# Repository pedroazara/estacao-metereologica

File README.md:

# Skylog — Estação Meteorológica Móvel

O Skylog é uma estação portátil para coletar dados ambientais durante
percursos. O sistema combina sensores conectados a um ESP32 com os recursos do
telefone, registra cada coleta localmente e envia os resultados para uma base
com site de visualização e análise.

## Versão documentada

Estado local analisado em **10/10/2026**, baseado no commit
`2cd59777b90f2dd33dc27cc1e1f5b2505c5105bb`, com alterações locais anteriores.
A V1 é uma meta de montagem; o aplicativo declara `1.0.0+1`.
Consulte a [documentação técnica consolidada](docs/versoes/2026-10-10-2cd5977-local/documentacao-tecnica.md) e o
[inventário de READMEs](docs/versoes/2026-10-10-2cd5977-local/cobertura-readmes.md).

## Estado da versão 1

O **aplicativo**, o **site** e o **sistema de coleta e sincronização** têm
implementação e testes locais. A V1 ainda precisa de integração de software e
validação física, além de finalizar o hardware:

- integrar ENS160+AHT21 no firmware principal, contrato BLE, aplicativo e base;
- alinhar o firmware ao conversor automático e à retirada dos sensores antigos;
- concluir o projeto da placa de circuito impresso;
- usinar a placa na CNC e montar os componentes;
- validar o conjunto completo de sensores;
- projetar e imprimir a caixa.

O firmware atual ainda consulta WTGAHRS3, KY-013 e KY-038, e o aplicativo
oferece KY-013/KY-038 na seleção. O ENS160+AHT21 existe apenas em sketch de
teste; ainda não é transmitido pelo firmware principal nem selecionável no app.
O som do telefone fica no JSONL, mas ainda não alimenta a medida de ruído no mapa.

## Sensores definidos para a montagem V1

| Origem | Sensor ou recurso | Medições |
|---|---|---|
| Estação | Sensor ambiental RS485 | Temperatura e umidade |
| Estação | KY-028 | Temperatura auxiliar |
| Estação | ENS160 + AHT21 | eCO₂ estimado, TVOC, índice de qualidade do ar, temperatura e umidade de compensação |
| Estação | GY-302 / BH1750 | Luminosidade em lux |
| Telefone | GPS | Posição, percurso, velocidade e rumo |
| Telefone | Microfone | Nível sonoro, sem armazenar o áudio |

O ENS160 é um sensor de qualidade do ar. O valor de eCO₂ é uma estimativa
calculada a partir dos gases detectados, não uma medição direta da concentração
de dióxido de carbono. O AHT21 fornece temperatura e umidade para compensar as
leituras do ENS160.

## Funcionamento

```text
Sensor RS485 ────────────┐
KY-028 ──────────────────┤
ENS160 + AHT21 (previsto)┼── ESP32 ── Bluetooth ── aplicativo
GY-302 / BH1750 ─────────┘                           + GPS do telefone
                                                     + nível sonoro
                                                            │
                                                    coleta em JSONL
                                                            │
                                                sincronização pela rede
                                                            │
                                                            ▼
                                               base de processamento
                                                            │
                                                            ▼
                                                  site de visualização
```

O ESP32 lê RS485, KY-028 e BH1750 e transmite os dados ao aplicativo por
Bluetooth Low Energy. O aplicativo acrescenta a localização e o nível sonoro
obtidos pelo telefone, registra a coleta e mantém o arquivo salvo localmente.
Quando a base está acessível, a sessão pode ser sincronizada pela rede.

A base recebe os arquivos, preserva os dados coletados, processa as medições e
disponibiliza os resultados no site. A indisponibilidade da base durante o
trabalho de campo não interrompe a coleta no telefone. Entretanto, no firmware
atual o modo de configuração Wi-Fi anuncia BLE, mas retorna antes da aquisição
e publicação dos sensores. O funcionamento completo sem rede Wi-Fi no arranque
continua pendente.

## Divisão de responsabilidades

| Componente | Responsabilidade |
|---|---|
| ESP32 | Ler os sensores externos e transmitir as medições por Bluetooth |
| Aplicativo | Receber as leituras, coletar GPS e nível sonoro, gravar e sincronizar as sessões |
| Base | Armazenar e processar as coletas recebidas |
| Site | Exibir sessões, trajetos e medições |
| Placa de interface | Reunir ESP32, alimentação, conversor RS485 e conexões dos sensores |

## Hardware da estação

Os sensores ficam externos à placa de interface e são ligados por cabos:

- o sensor ambiental utiliza RS485 por meio de um conversor conectado à UART
  do ESP32;
- o KY-028 utiliza uma entrada analógica;
- o ENS160+AHT21 e o GY-302/BH1750 compartilham o barramento I²C;
- o ESP32 concentra as leituras e a comunicação Bluetooth com o telefone.

A placa está sendo projetada no KiCad e será fabricada por **usinagem CNC**.
Antes da usinagem serão conferidas a pinagem, as tensões, os conectores, as
dimensões dos módulos, a posição da antena do ESP32 e a compatibilidade das
trilhas e folgas com as ferramentas disponíveis. A caixa será projetada depois
da montagem definitiva, para que as aberturas, fixações e ventilação acompanhem
as dimensões reais.

## Formato e fluxo da coleta

As sessões são gravadas no telefone em JSONL, com um registro por linha. Esse
formato permite acrescentar medições continuamente e preserva as linhas já
gravadas mesmo se a coleta for interrompida.

O fluxo principal é:

1. o aplicativo conecta à estação por Bluetooth;
2. a pessoa seleciona os sensores e confere as leituras;
3. o aplicativo grava os dados ambientais, a posição e o nível sonoro;
4. a sessão permanece armazenada no telefone;
5. o arquivo é enviado para a base quando ela estiver disponível;
6. os dados processados podem ser consultados no site.

## Estrutura do projeto

| Pasta | Conteúdo |
|---|---|
| [`app/`](app/) | Aplicativo Flutter para Android |
| [`firmware/`](firmware/) | Firmware e testes dos sensores conectados ao ESP32 |
| [`hardware/skylog/`](hardware/skylog/) | Esquema, PCB e documentação da placa de interface |
| [`src/`](src/) | Servidor, processamento e site da base |
| [`docs/`](docs/) | Documentação técnica da arquitetura e da implantação |
| [`servidor/`](servidor/) | Arquivos de configuração da base |
| [`docs/organizacao/`](docs/organizacao/2026-10-10/relatorio.md) | Organização técnica, limpeza e rastreabilidade |
| [`ferramentas/cnc-jog/`](ferramentas/cnc-jog/LEIA-ME.txt) | Ferramenta local auxiliar da oficina, ainda não versionada no commit-base |

## Organização técnica

O [índice do hardware](hardware/README.md) aponta para a variante em desenvolvimento,
a referência bicamada, as bibliotecas e os arquivos de fabricação. Backups,
recuperações e testes obsoletos foram removidos conforme o
[relatório de limpeza](docs/organizacao/2026-10-10/relatorio.md).
O firmware, o app, a base e os dados mantêm suas pastas próprias.

## Documentação

- [Aplicativo Android](app/README.md)
- [Firmware e ligações dos sensores](firmware/README.md)
- [Arquitetura e telemetria](docs/04-telemetria.md)
- [Base de processamento](docs/05-base-raspberry-pi.md)
- [Placa de circuito impresso](hardware/skylog/README.md)

## Executar a base e conferir o software

Na raiz do repositório, `python3 src/servidor_telemetria.py --porta 8771` inicia
a base. Abra `http://localhost:8771` no navegador. Esse servidor usa a biblioteca
padrão do Python e SQLite; não precisa de Mosquitto. O mapa carrega Leaflet e
mapas online. Preparação do Android: [app/README.md](app/README.md).

Verificações locais: na pasta `app`, com dependências já disponíveis,
`flutter test --no-pub` e
`flutter analyze --no-pub`. Em 10/10/2026 passaram 7 testes Python e 66 Flutter;
a análise apontou uma ocorrência informativa de estilo preexistente. Os 7 testes
Python eram do filtro legado e foram removidos na limpeza posterior; os testes
do aplicativo permanecem. O painel CNC possui testes próprios em `ferramentas/`.

## Etapas para concluir a V1

- [ ] Integrar ENS160+AHT21 de ponta a ponta e retirar opções antigas da coleta V1.
- [ ] Resolver aquisição no modo de configuração Wi-Fi e alinhar `PINO_DE`.
- [ ] Integrar som do telefone ao processamento e à visualização da base.

- [ ] Finalizar o esquema e o leiaute da PCB.
- [ ] Conferir os módulos, footprints, conectores e tensões com os componentes
  reais.
- [ ] Definir ferramentas, profundidades e origem da variante escolhida; na
  bicamada, definir alinhamento entre faces.
- [ ] Gerar os percursos e o G-code de isolamento, furação e recorte.
- [ ] Usinar a placa na CNC e inspecionar continuidade, curtos e alinhamento.
- [ ] Montar e testar alimentação, RS485, I²C, entrada analógica, Bluetooth e
  Wi-Fi.
- [ ] Executar uma coleta completa com o hardware definitivo.
- [ ] Projetar e imprimir a caixa.

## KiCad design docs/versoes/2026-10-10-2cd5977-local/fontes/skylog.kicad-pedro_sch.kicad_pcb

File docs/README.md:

# Documentação técnica

- [Documento consolidado](versoes/2026-10-10-2cd5977-local/documentacao-tecnica.md): captura do estado analisado em 10/10/2026, com imagens, fontes, limitações e evidências.
- [Organização e limpeza](organizacao/2026-10-10/relatorio.md): estrutura atual, movimentos, remoções e verificações.
- [Arquitetura e telemetria](04-telemetria.md): fluxo atual e decisões anteriores identificadas como históricas.
- [Base Raspberry Pi](05-base-raspberry-pi.md): operação atual por HTTP e notas de implantação.
- [Hardware](../hardware/README.md), [firmware](../firmware/README.md) e [aplicativo](../app/README.md): entradas de cada componente.

Os documentos `01`, `02` e `03` registram conhecimentos de conexão, protocolo
WTG e Kalman. São referências técnicas históricas. Os testes/exercícios antigos
foram removidos a pedido; a matemática e os registros documentais foram mantidos.
A pasta `versoes` preserva a captura da análise, mesmo quando um arquivo-fonte
antigo deixa de fazer parte da árvore ativa.

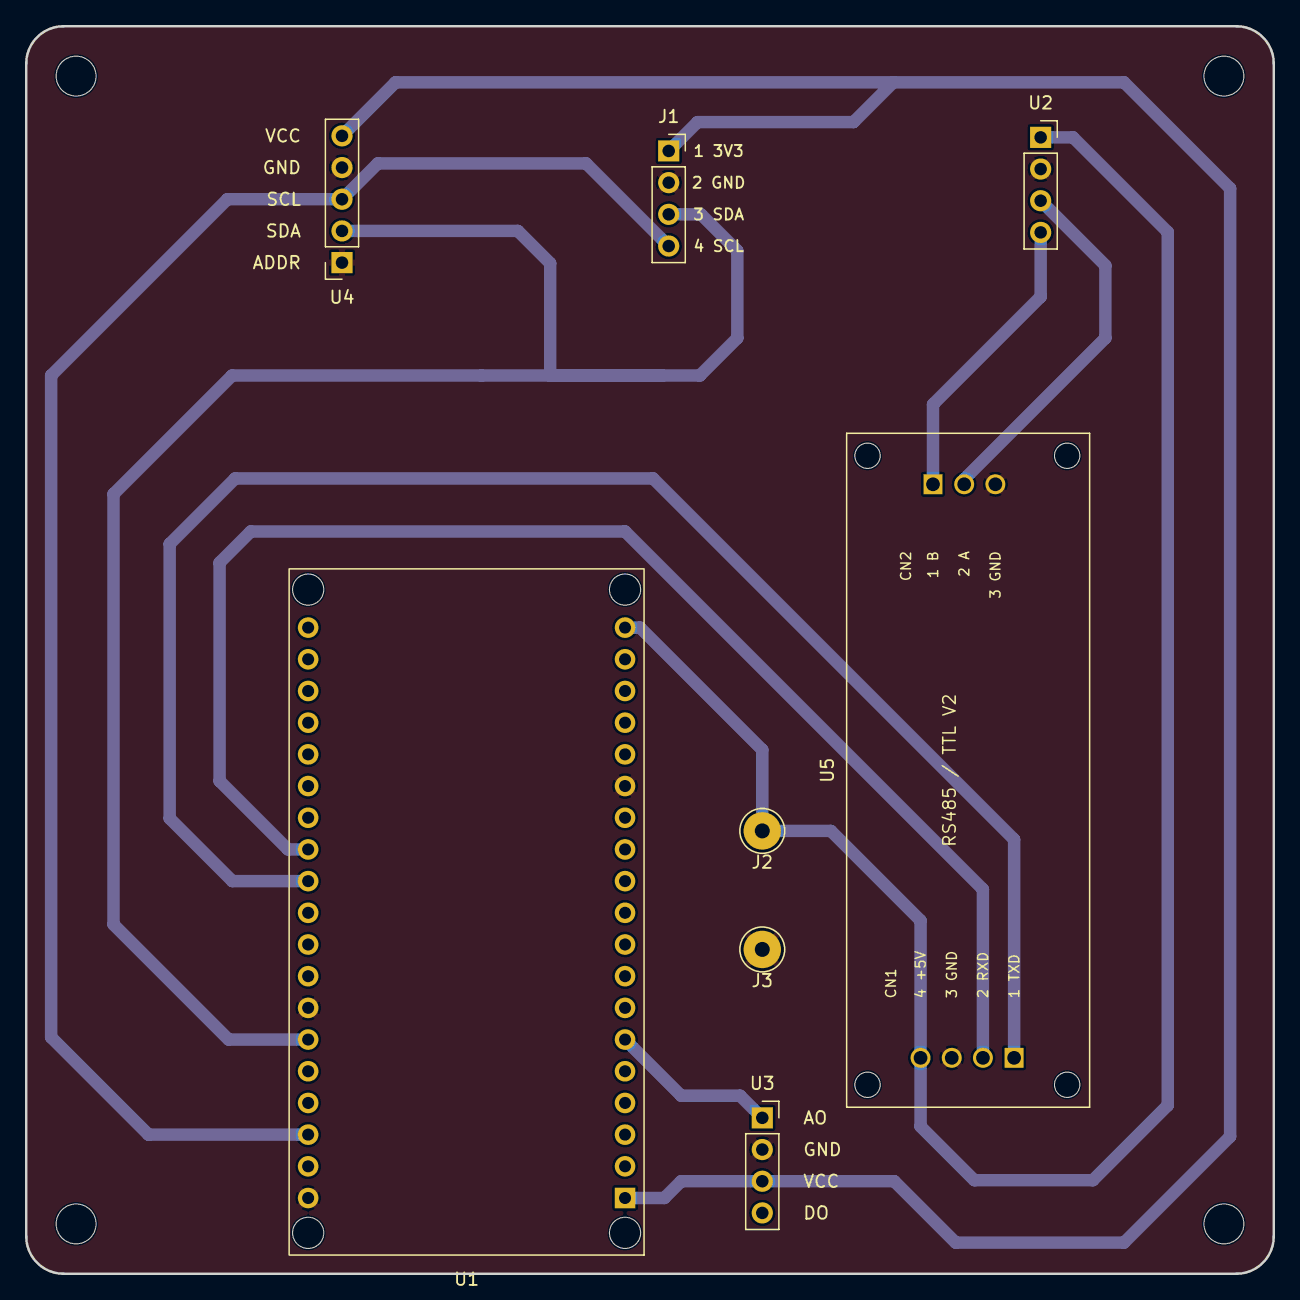
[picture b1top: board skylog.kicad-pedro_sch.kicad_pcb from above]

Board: 2 copper layers, 100.0 x 100.0 mm, 12 parts (0 on the bottom side), 10 nets.

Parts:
H2, H3, H4, H5: MountingHole_Pad; MountingHole_3.2mm_M3
J1: Sensor de Qualidade do Ar ENS160+AHT21; ENS160_AHT21_1x04_P2.54mm
J2: WEMOS_5V; Wire_Pad_D1.2mm
J3: WEMOS_GND; Wire_Pad_D1.2mm
U1: ESP32-DevKitC; ESP32_NodeMCU_38Pin_4Furos_AConferir
U2: Sensor de Temperatura e Umidade RS485; PinSocket_1x04_P2.54mm_Vertical
U3: Sensor de Temperatura KY-028; KY-028_Conector_1x04_P2.54mm
U4: Sensor de Luminosidade GY-302; GY-302_Conector_1x05_P2.54mm
U5: Conversor RS485/TTL; RS485_TTL_V2_OSHWLab_PadGeometry

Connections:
+3.3V: J1.1, U1.1 (3V3), U3.3 (VCC), U4.5 (VCC)
+5V: J2.1 (~_1), U1.19 (5V), U2.1 (VIN), U5.CN1.4 (+5V)
/RS485_A: U2.3 (RS485_A+), U5.CN2.2 (A)
/RS485_B: U2.4 (RS485_B-), U5.CN2.1 (B)
/RS485_RX: U1.27 (GPIO16), U5.CN1.2 (RXD)
/RS485_TX: U1.28 (GPIO17), U5.CN1.1 (TXD)
GND: J1.2, J3.1 (~_1), U1.14 (GND), U1.32 (GND), U1.38 (GND), U2.2 (GND), U3.2 (GND), U4.1 (ADDR), U4.4 (GND), U5.CN1.3 (GND_TTL), U5.CN2.3 (GND_RS485)
unnamed: J1.3, U1.33 (GPIO21), U4.2 (SDA)
unnamed: J1.4, U1.36 (GPIO22), U4.3 (SCL)
unnamed: U1.6 (VDET_2/GPIO35/ADC1_CH7), U3.1 (AO)
